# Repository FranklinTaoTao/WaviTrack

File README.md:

# WaviTrack

> [!NOTE]
> Looking for our main conference paper? Read [*WaviTrack: Exploiting Body-Area RF Channels for Wearable Human Motion Reconstruction*](https://doi.org/10.1145/3830727.3834831). For its simulation, ML models, and motion-reconstruction code, see [FranklinTaoTao/WaviTrack-RF-Motion](https://github.com/FranklinTaoTao/WaviTrack-RF-Motion).

*An assembled node, from Figure 1a of the [workshop paper](https://doi.org/10.1145/3798063.3837383) (CC BY 4.0).*

This repository accompanies our workshop paper, [*From PCB to Packets: An Open Hardware and Firmware Foundation for Reproducible Wearable Motion Capture*](https://doi.org/10.1145/3798063.3837383), presented at **Reproduce: The 1st Workshop on Reproducible Methods for Wearable Sensing and Ubiquitous Computing** during **UbiComp/ISWC 2026**. The paper appears in the *UbiComp Companion '26* proceedings.

WaviTrack covers the wearable measurement path from board design to IMU, UWB range, and CIR packets.

## Contents

- `hardware/v2/`: XIAO ESP32-C3/BNO055 board; KiCad design, BOM, and fabrication files.
- `hardware/v3/`: XIAO ESP32-C6/BNO085 board; KiCad design, BOM, and fabrication files.
- `enclosure/`: printable PCB carrier and strap mount for both board revisions.
- `firmware/`: modified DW3000 driver, board examples, V3 six-node collection, and Python capture tools. See the [firmware guide](firmware/README.md).

Use the KiCad files, BOM, and `fabrication/` outputs from the **same revision** when making a board. During assembly, keep the UWB antenna region clear and orient the board consistently in its carrier. For a first radio check, use the pairwise ranging sketches before running six-node collection.

## License

WaviTrack-authored material is released under the Apache License, Version 2.0; see [LICENSE](LICENSE). The cover image is reproduced from the CC BY 4.0 workshop paper. Bundled third-party material keeps its own terms. In particular, the Seeed Studio XIAO KiCad library and its footprint copies are covered by [CC BY-SA 4.0](<hardware/v3/Seeed Studio XIAO Series Library/LICENSE.md>). See [NOTICE](NOTICE) and the notices in individual files for attribution.

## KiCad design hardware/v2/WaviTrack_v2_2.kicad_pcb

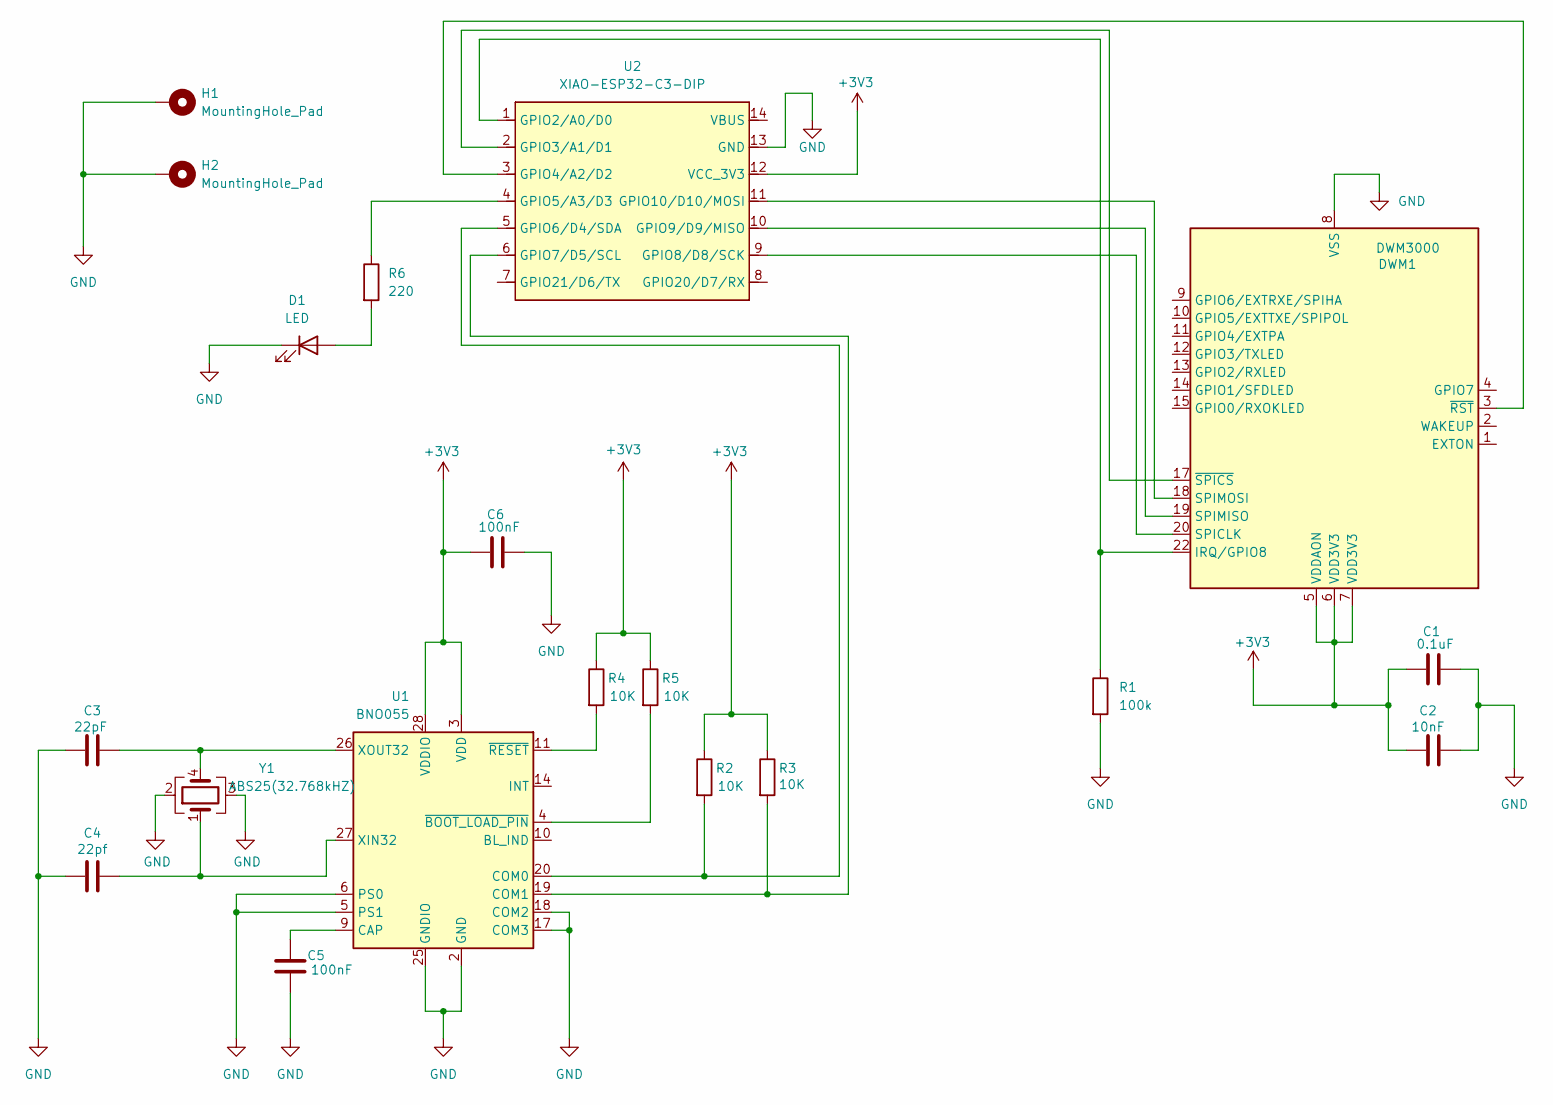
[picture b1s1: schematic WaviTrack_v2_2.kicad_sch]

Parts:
C1: 0.1uF; C_0603_1608Metric
C2: 10nF; C_0603_1608Metric
C3: 22pF; C_0603_1608Metric
C4: 22pf; C_0603_1608Metric
C5, C6: 100nF; C_0603_1608Metric
D1: LED; LED_0805_2012Metric
DWM1: DWM3000; DWM1000
H1, H2: MountingHole_Pad; MountingHole_3mm_Pad_TopBottom
R1: 100k; R_0805_2012Metric
R2, R3, R4, R5: 10K; R_0805_2012Metric
R6: 220; R_0805_2012Metric
U1: BNO055; LGA-28_5.2x3.8mm_P0.5mm
U2: XIAO-ESP32-C3-DIP; XIAO-ESP32C3-DIP
Y1: ABS25(32.768kHZ); Crystal_SMD_Abracon_ABS25-4Pin_8.0x3.8mm

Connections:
+3V3: C1.1, C2.1, C6.1, DWM1.5 (VDDAON), DWM1.6 (VDD3V3), DWM1.7 (VDD3V3), R2.1, R3.1, R4.1, R5.1, U1.3 (VDD), U1.28 (VDDIO), U2.12 (VCC_3V3)
GND: C1.2, C2.2, C3.1, C4.1, C5.2, C6.2, D1.1 (K), DWM1.8 (VSS), DWM1.16 (VSS), DWM1.21 (VSS), DWM1.23 (VSS), DWM1.24 (VSS), H1.1, H2.1, R1.2, U1.2 (GND), U1.5 (PS1), U1.6 (PS0), U1.17 (COM3), U1.18 (COM2), U1.25 (GNDIO), U2.13 (GND), Y1.2, Y1.3
unnamed: D1.2 (A), R6.2
unnamed: DWM1.22 (IRQ/GPIO8), R1.1, U2.1 (GPIO2/A0/D0)
unnamed: DWM1.20 (SPICLK), U2.9 (GPIO8/D8/SCK)
unnamed: DWM1.19 (SPIMISO), U2.10 (GPIO9/D9/MISO)
unnamed: DWM1.18 (SPIMOSI), U2.11 (GPIO10/D10/MOSI)
unnamed: DWM1.3 (~RST), U2.3 (GPIO4/A2/D2)
unnamed: DWM1.17 (~SPICS), U2.2 (GPIO3/A1/D1)
unnamed: C5.1, U1.9 (CAP)
unnamed: R2.2, U1.20 (COM0), U2.5 (GPIO6/D4/SDA)
unnamed: R3.2, U1.19 (COM1), U2.6 (GPIO7/D5/SCL)
unnamed: C4.2, U1.27 (XIN32), Y1.1
unnamed: C3.2, U1.26 (XOUT32), Y1.4
unnamed: R5.2, U1.4 (~BOOT_LOAD_PIN)
unnamed: R4.2, U1.11 (~RESET)
unnamed: R6.1, U2.4 (GPIO5/A3/D3)

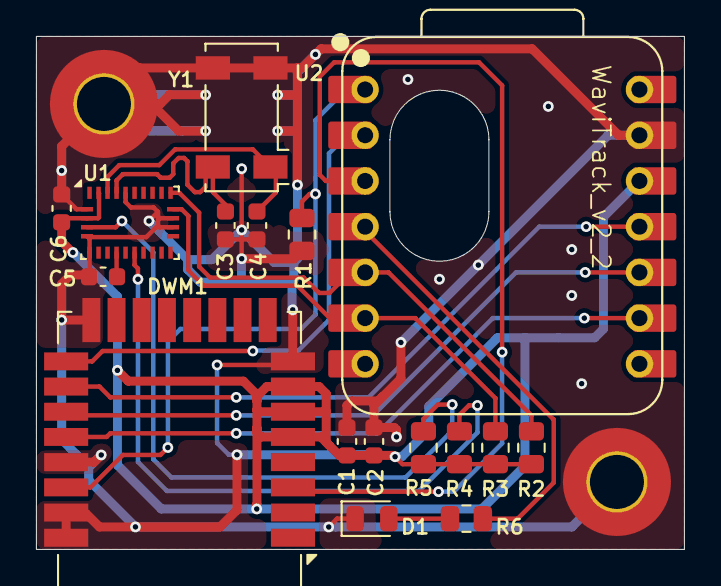
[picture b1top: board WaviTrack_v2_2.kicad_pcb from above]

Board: 2 copper layers, 36.0 x 28.5 mm, 19 parts (0 on the bottom side), 17 nets.

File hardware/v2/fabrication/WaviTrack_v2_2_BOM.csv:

"Refs","Value","Footprint","Qty","DNP"
"C1","0.1uF","Capacitor_SMD:C_0603_1608Metric","1",""
"C2","10nF","Capacitor_SMD:C_0603_1608Metric","1",""
"C3","22pF","Capacitor_SMD:C_0603_1608Metric","1",""
"C4","22pf","Capacitor_SMD:C_0603_1608Metric","1",""
"C5","100nF","Capacitor_SMD:C_0603_1608Metric","1",""
"C6","100nF","Capacitor_SMD:C_0603_1608Metric","1",""
"D1","LED","LED_SMD:LED_0805_2012Metric","1",""
"DWM1","DWM3000","RF_Module:DWM1000","1",""
"R1","100k","Resistor_SMD:R_0805_2012Metric","1",""
"R2","10K","Resistor_SMD:R_0805_2012Metric","1",""
"R3","10K","Resistor_SMD:R_0805_2012Metric","1",""
"R4","10K","Resistor_SMD:R_0805_2012Metric","1",""
"R5","10K","Resistor_SMD:R_0805_2012Metric","1",""
"R6","220","Resistor_SMD:R_0805_2012Metric","1",""
"U1","BNO055","Package_LGA:LGA-28_5.2x3.8mm_P0.5mm","1",""
"U2","XIAO-ESP32-C3-DIP","Seeed Studio XIAO Series Library:XIAO-ESP32C3-DIP","1",""
"Y1","ABS25(32.768kHZ)","Crystal:Crystal_SMD_Abracon_ABS25-4Pin_8.0x3.8mm","1",""

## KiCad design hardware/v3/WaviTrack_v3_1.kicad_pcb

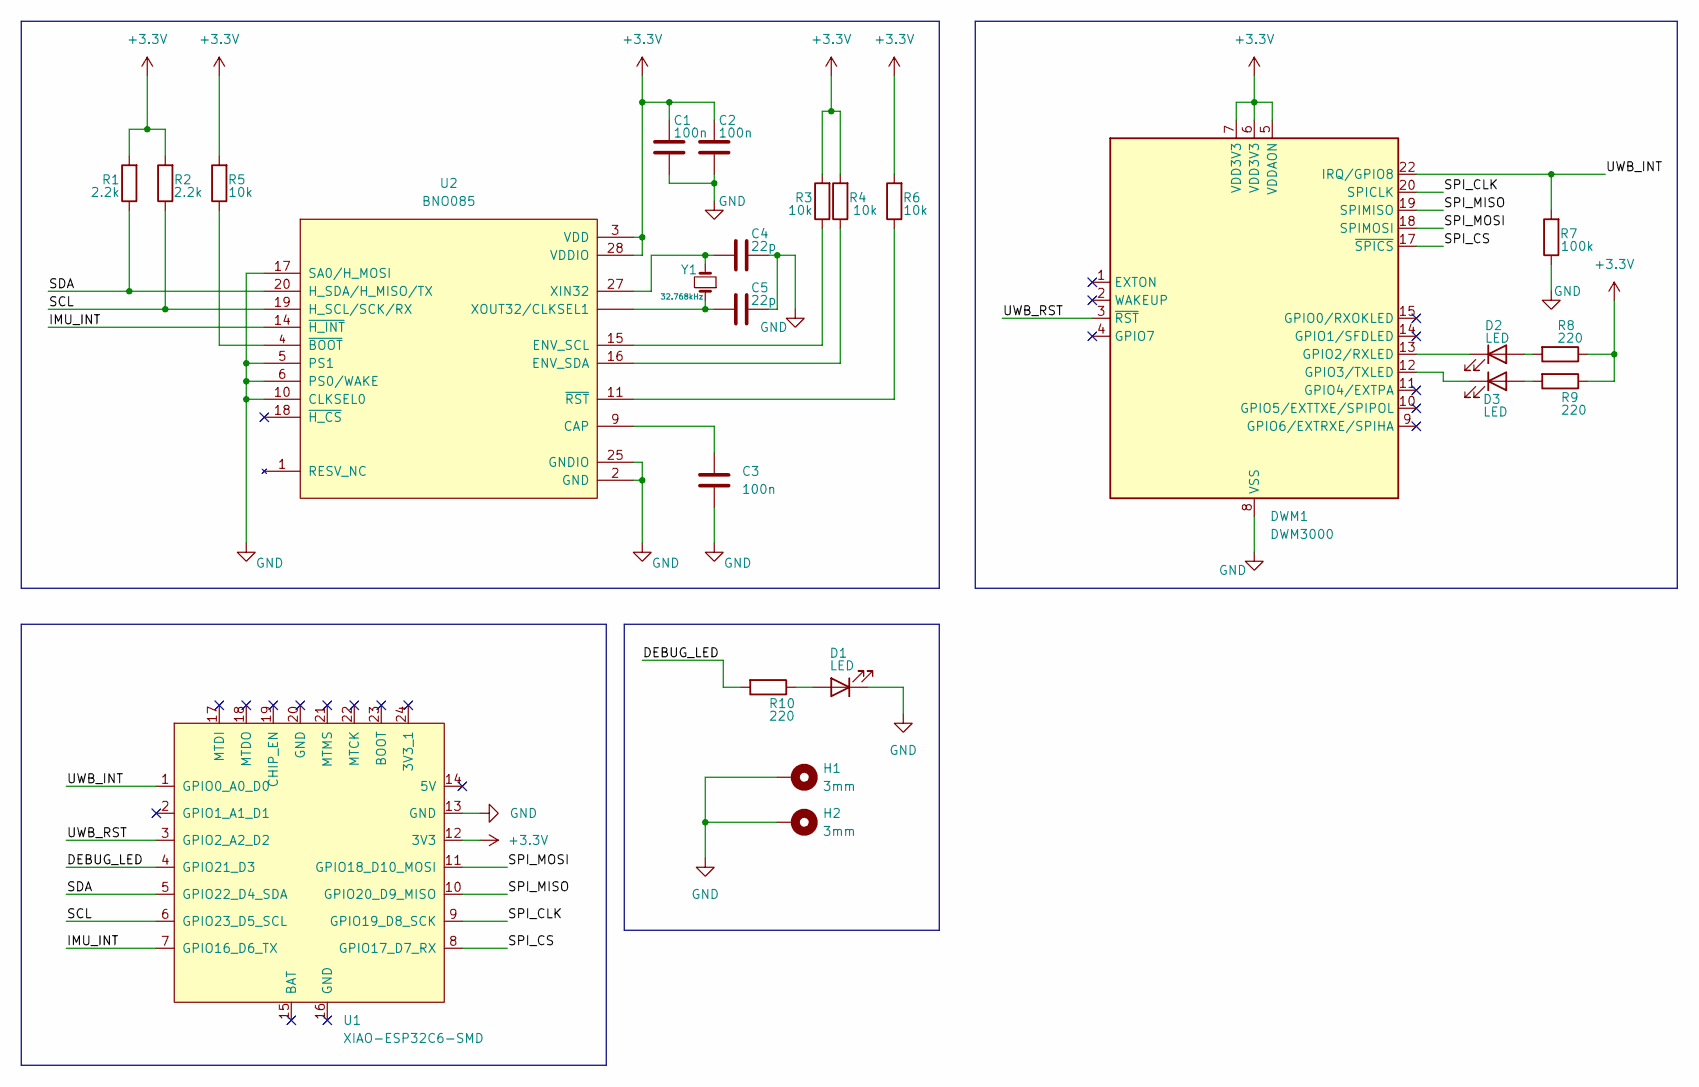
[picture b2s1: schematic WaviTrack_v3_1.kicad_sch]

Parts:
C1, C2, C3: 100n; C_0603_1608Metric
C4, C5: 22p; C_0603_1608Metric
D1, D2, D3: LED; LED_0603_1608Metric
DWM1: DWM3000; DWM1000
H1, H2: 3mm; MountingHole_3mm_Pad_TopBottom
R1, R2: 2.2k; R_0603_1608Metric
R3, R4, R5, R6: 10k; R_0603_1608Metric
R7: 100k; R_0603_1608Metric
R8, R9, R10: 220; R_0603_1608Metric
U1: XIAO-ESP32C6-SMD
U2: BNO085; IC_BNO085; PARTREV v1.17
Y1: 32.768kHz; Crystal_SMD_3215-2Pin_3.2x1.5mm

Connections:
+3.3V: C1.1, C2.1, DWM1.5 (VDDAON), DWM1.6 (VDD3V3), DWM1.7 (VDD3V3), R1.2, R2.2, R3.2, R4.2, R5.2, R6.2, R8.1, R9.1, U1.12 (3V3), U2.3 (VDD), U2.28 (VDDIO); also elsewhere on the board
/DEBUG_LED: R10.2, U1.4 (GPIO21_D3)
/IMU_INT: U1.7 (GPIO16_D6_TX), U2.14 (~H_INT)
/SCL: R2.1, U1.6 (GPIO23_D5_SCL), U2.19 (H_SCL/SCK/RX)
/SDA: R1.1, U1.5 (GPIO22_D4_SDA), U2.20 (H_SDA/H_MISO/TX)
/SPI_CLK: DWM1.20 (SPICLK), U1.9 (GPIO19_D8_SCK); also elsewhere on the board
/SPI_CS: DWM1.17 (~SPICS), U1.8 (GPIO17_D7_RX); also elsewhere on the board
/SPI_MISO: DWM1.19 (SPIMISO), U1.10 (GPIO20_D9_MISO); also elsewhere on the board
/SPI_MOSI: DWM1.18 (SPIMOSI), U1.11 (GPIO18_D10_MOSI); also elsewhere on the board
/UWB_INT: DWM1.22 (IRQ/GPIO8), R7.2, U1.1 (GPIO0_A0_D0); also elsewhere on the board
/UWB_RST: DWM1.3 (~RST), U1.3 (GPIO2_A2_D2); also elsewhere on the board
GND: C1.2, C2.2, C3.2, C4.1, C5.1, D1.1 (K), DWM1.8 (VSS), DWM1.16 (VSS), DWM1.21 (VSS), DWM1.23 (VSS), DWM1.24 (VSS), H1.1, H2.1, R7.1, U1.13 (GND), U2.2 (GND), U2.5 (PS1), U2.6 (PS0/WAKE), U2.10 (CLKSEL0), U2.17 (SA0/H_MOSI), U2.25 (GNDIO); also elsewhere on the board
unnamed: D1.2 (A), R10.1
unnamed: D2.2 (A), R8.2
unnamed 14: D2.1 (K), DWM1.13 (GPIO2/RXLED); also elsewhere on the board
unnamed: D3.2 (A), R9.2
unnamed 16: D3.1 (K), DWM1.12 (GPIO3/TXLED); also elsewhere on the board
unnamed: C3.1, U2.9 (CAP)
unnamed: R3.1, U2.15 (ENV_SCL)
unnamed: R4.1, U2.16 (ENV_SDA)
unnamed: C4.2, U2.27 (XIN32), Y1.2
unnamed: C5.2, U2.26 (XOUT32/CLKSEL1), Y1.1
unnamed: R5.1, U2.4 (~BOOT)
unnamed: R6.1, U2.11 (~RST)

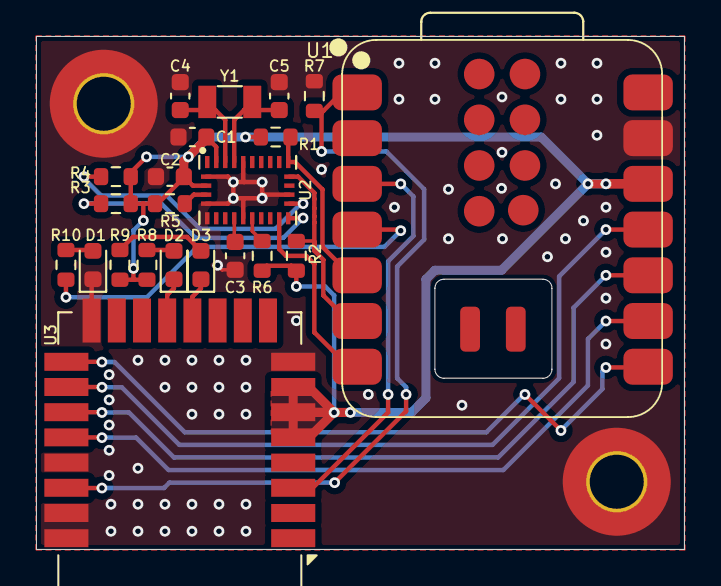
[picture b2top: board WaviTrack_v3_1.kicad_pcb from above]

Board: 4 copper layers, 36.0 x 28.5 mm, 24 parts (0 on the bottom side), 24 nets.

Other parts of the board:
U3: DWM3000; DWM1000

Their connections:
+3.3V: U3.5 (VDDAON), U3.6 (VDD3V3), U3.7 (VDD3V3); also elsewhere on the board
/SPI_CLK: U3.20 (SPICLK); also elsewhere on the board
/SPI_CS: U3.17 (~SPICS); also elsewhere on the board
/SPI_MISO: U3.19 (SPIMISO); also elsewhere on the board
/SPI_MOSI: U3.18 (SPIMOSI); also elsewhere on the board
/UWB_INT: U3.22 (IRQ/GPIO8); also elsewhere on the board
/UWB_RST: U3.3 (~RST); also elsewhere on the board
GND: U3.8 (VSS), U3.16 (VSS), U3.21 (VSS), U3.23 (VSS), U3.24 (VSS); also elsewhere on the board
unnamed 14: U3.13 (GPIO2/RXLED); also elsewhere on the board
unnamed 16: U3.12 (GPIO3/TXLED); also elsewhere on the board

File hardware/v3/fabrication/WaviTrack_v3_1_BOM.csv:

"Refs","Value","Footprint","Qty","DNP"
"C1","100n","Capacitor_SMD:C_0603_1608Metric","1",""
"C2","100n","Capacitor_SMD:C_0603_1608Metric","1",""
"C3","100n","Capacitor_SMD:C_0603_1608Metric","1",""
"C4","22p","Capacitor_SMD:C_0603_1608Metric","1",""
"C5","22p","Capacitor_SMD:C_0603_1608Metric","1",""
"D1","LED","LED_SMD:LED_0603_1608Metric","1",""
"D2","LED","LED_SMD:LED_0603_1608Metric","1",""
"D3","LED","LED_SMD:LED_0603_1608Metric","1",""
"DWM1","DWM3000","RF_Module:DWM1000","1",""
"R1","2.2k","Resistor_SMD:R_0603_1608Metric","1",""
"R2","2.2k","Resistor_SMD:R_0603_1608Metric","1",""
"R3","10k","Resistor_SMD:R_0603_1608Metric","1",""
"R4","10k","Resistor_SMD:R_0603_1608Metric","1",""
"R5","10k","Resistor_SMD:R_0603_1608Metric","1",""
"R6","10k","Resistor_SMD:R_0603_1608Metric","1",""
"R7","100k","Resistor_SMD:R_0603_1608Metric","1",""
"R8","220","Resistor_SMD:R_0603_1608Metric","1",""
"R9","220","Resistor_SMD:R_0603_1608Metric","1",""
"R10","220","Resistor_SMD:R_0603_1608Metric","1",""
"U1","XIAO-ESP32C6-SMD","Xiao:XIAO-ESP32C6-SMD","1",""
"U2","BNO085","WaviTrack:IC_BNO085","1",""
"Y1","32.768kHz","Crystal:Crystal_SMD_3215-2Pin_3.2x1.5mm","1",""
